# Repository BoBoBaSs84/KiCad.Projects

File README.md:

# KiCad.Projects
All of my KiCad projects are stored here.

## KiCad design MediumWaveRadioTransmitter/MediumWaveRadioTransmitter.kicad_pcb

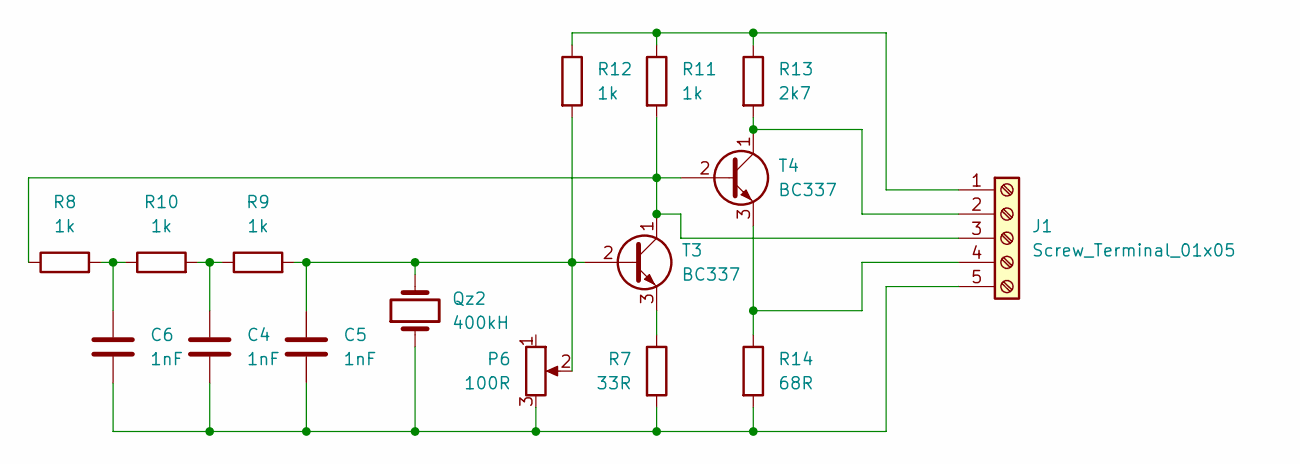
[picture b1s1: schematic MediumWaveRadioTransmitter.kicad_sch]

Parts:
C4, C5: 1nF; C_Disc_D4.3mm_W1.9mm_P5.00mm
C6: 1nF; C_Disc_D4.7mm_W2.5mm_P5.00mm
J1: Screw_Terminal_01x05; Wuerth_WR-WTB_64800511622_1x05_P1.50mm_Vertical
P6: 100R; Potentiometer_Bourns_3296W_Vertical
Qz2: 400kH; Resonator-2Pin_W8.0mm_H3.5mm
R7: 33R; R_Axial_DIN0204_L3.6mm_D1.6mm_P1.90mm_Vertical
R8, R9, R10, R11, R12: 1k; R_Axial_DIN0204_L3.6mm_D1.6mm_P1.90mm_Vertical
R13: 2k7; R_Axial_DIN0204_L3.6mm_D1.6mm_P1.90mm_Vertical
R14: 68R; R_Axial_DIN0204_L3.6mm_D1.6mm_P1.90mm_Vertical
T3, T4: BC337; TO-92

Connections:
unnamed: C4.1, R9.1, R10.2
unnamed: C6.1, R8.2, R10.1
unnamed: J1.1, R11.1, R12.1, R13.1
unnamed: J1.2, R13.2, T4.1 (C)
unnamed: J1.3, R8.1, R11.2, T3.1 (C), T4.2 (B)
unnamed: J1.4, R14.1, T4.3 (E)
unnamed: C4.2, C5.2, C6.2, J1.5, P6.3, Qz2.1, R7.2, R14.2
unnamed: C5.1, P6.2, Qz2.2, R9.2, R12.2, T3.2 (B)
unnamed: R7.1, T3.3 (E)

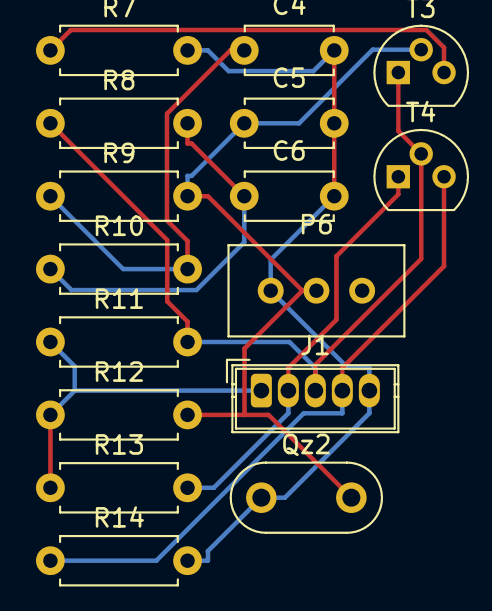
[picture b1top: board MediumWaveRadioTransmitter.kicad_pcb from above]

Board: 2 copper layers, 16 parts (0 on the bottom side), 9 nets.

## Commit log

2024-01-06 chore: updated README.md
2024-01-06 chore: created CODE_OF_CONDUCT.md
2024-01-06 feat: added mwrt
2024-01-27 feat: circuit diagram improved
2024-01-27 feat: circuit diagram improved
    changes:
    - circuit diagram improved
    - pcb layout routed
    closes #1
